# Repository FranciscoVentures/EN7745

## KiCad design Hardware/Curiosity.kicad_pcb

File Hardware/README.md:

Intro
=======

Curiosity™ EN7745
Developed by Francisco Ventures™

Based on the open source hardware project USB Armory MK II | https://github.com/f-secure-foundry/usbarmory/tree/master/hardware/mark-two

DISCLAIMER
=======

Francisco Ventures™ (“Francisco”) is not responsible for typographical or other errors or omissions or for direct, indirect, incidental or consequential damages related to this material or resulting from its use. Francisco makes no warranty or representation respecting this material, which is provided on an "AS IS" basis. FRANCISCO HEREBY DISCLAIMS ALL WARRANTIES OR LIABILITY OF ANY KIND WITH RESPECT THERETO, INCLUDING, WITHOUT LIMITATION, REPRESENTATIONS REGARDING ACCURACY AND COMPLETENESS, ALL IMPLIED WARRANTIES AND CONDITIONS OF MERCHANTABILITY, SUITABILITY OR FITNESS FOR A PARTICULAR PURPOSE, TITLE AND/OR NON-INFRINGEMENT. This material is not designed, intended or authorized for use in medical, life support, life sustaining or nuclear applications or applications in which the failure of the product could result in personal injury, death or property damage. Any party using or selling products for use in any such applications do so at their sole risk and agree that Francisco is not liable, in whole or in part, for any claim or damage arising from such use, and agree to fully indemnify, defend and hold harmless Francisco from and against any and all claims, damages, loss, cost, expense or liability arising out of or in connection with the use or performance of products in such applications.

License
=======

This is an open hardware design licensed under the terms of the CERN Open
Hardware Licence (OHL) v1.2.

You may redistribute and modify this documentation under the terms of the CERN
OHL v.1.2 (http://ohwr.org/cernohl). This documentation is distributed WITHOUT
ANY EXPRESS OR IMPLIED WARRANTY, INCLUDING OF MERCHANTABILITY, SATISFACTORY
QUALITY AND FITNESS FOR A PARTICULAR PURPOSE. Please see the CERN OHL v.1.2 for
applicable conditions.

The following exceptions apply:

- ../lib.snapeda: all files in this directory are imported or modified
from SnapEDA symbols and footprints, therefore the license at
https://www.snapeda.com/about/FAQ/#license applies.

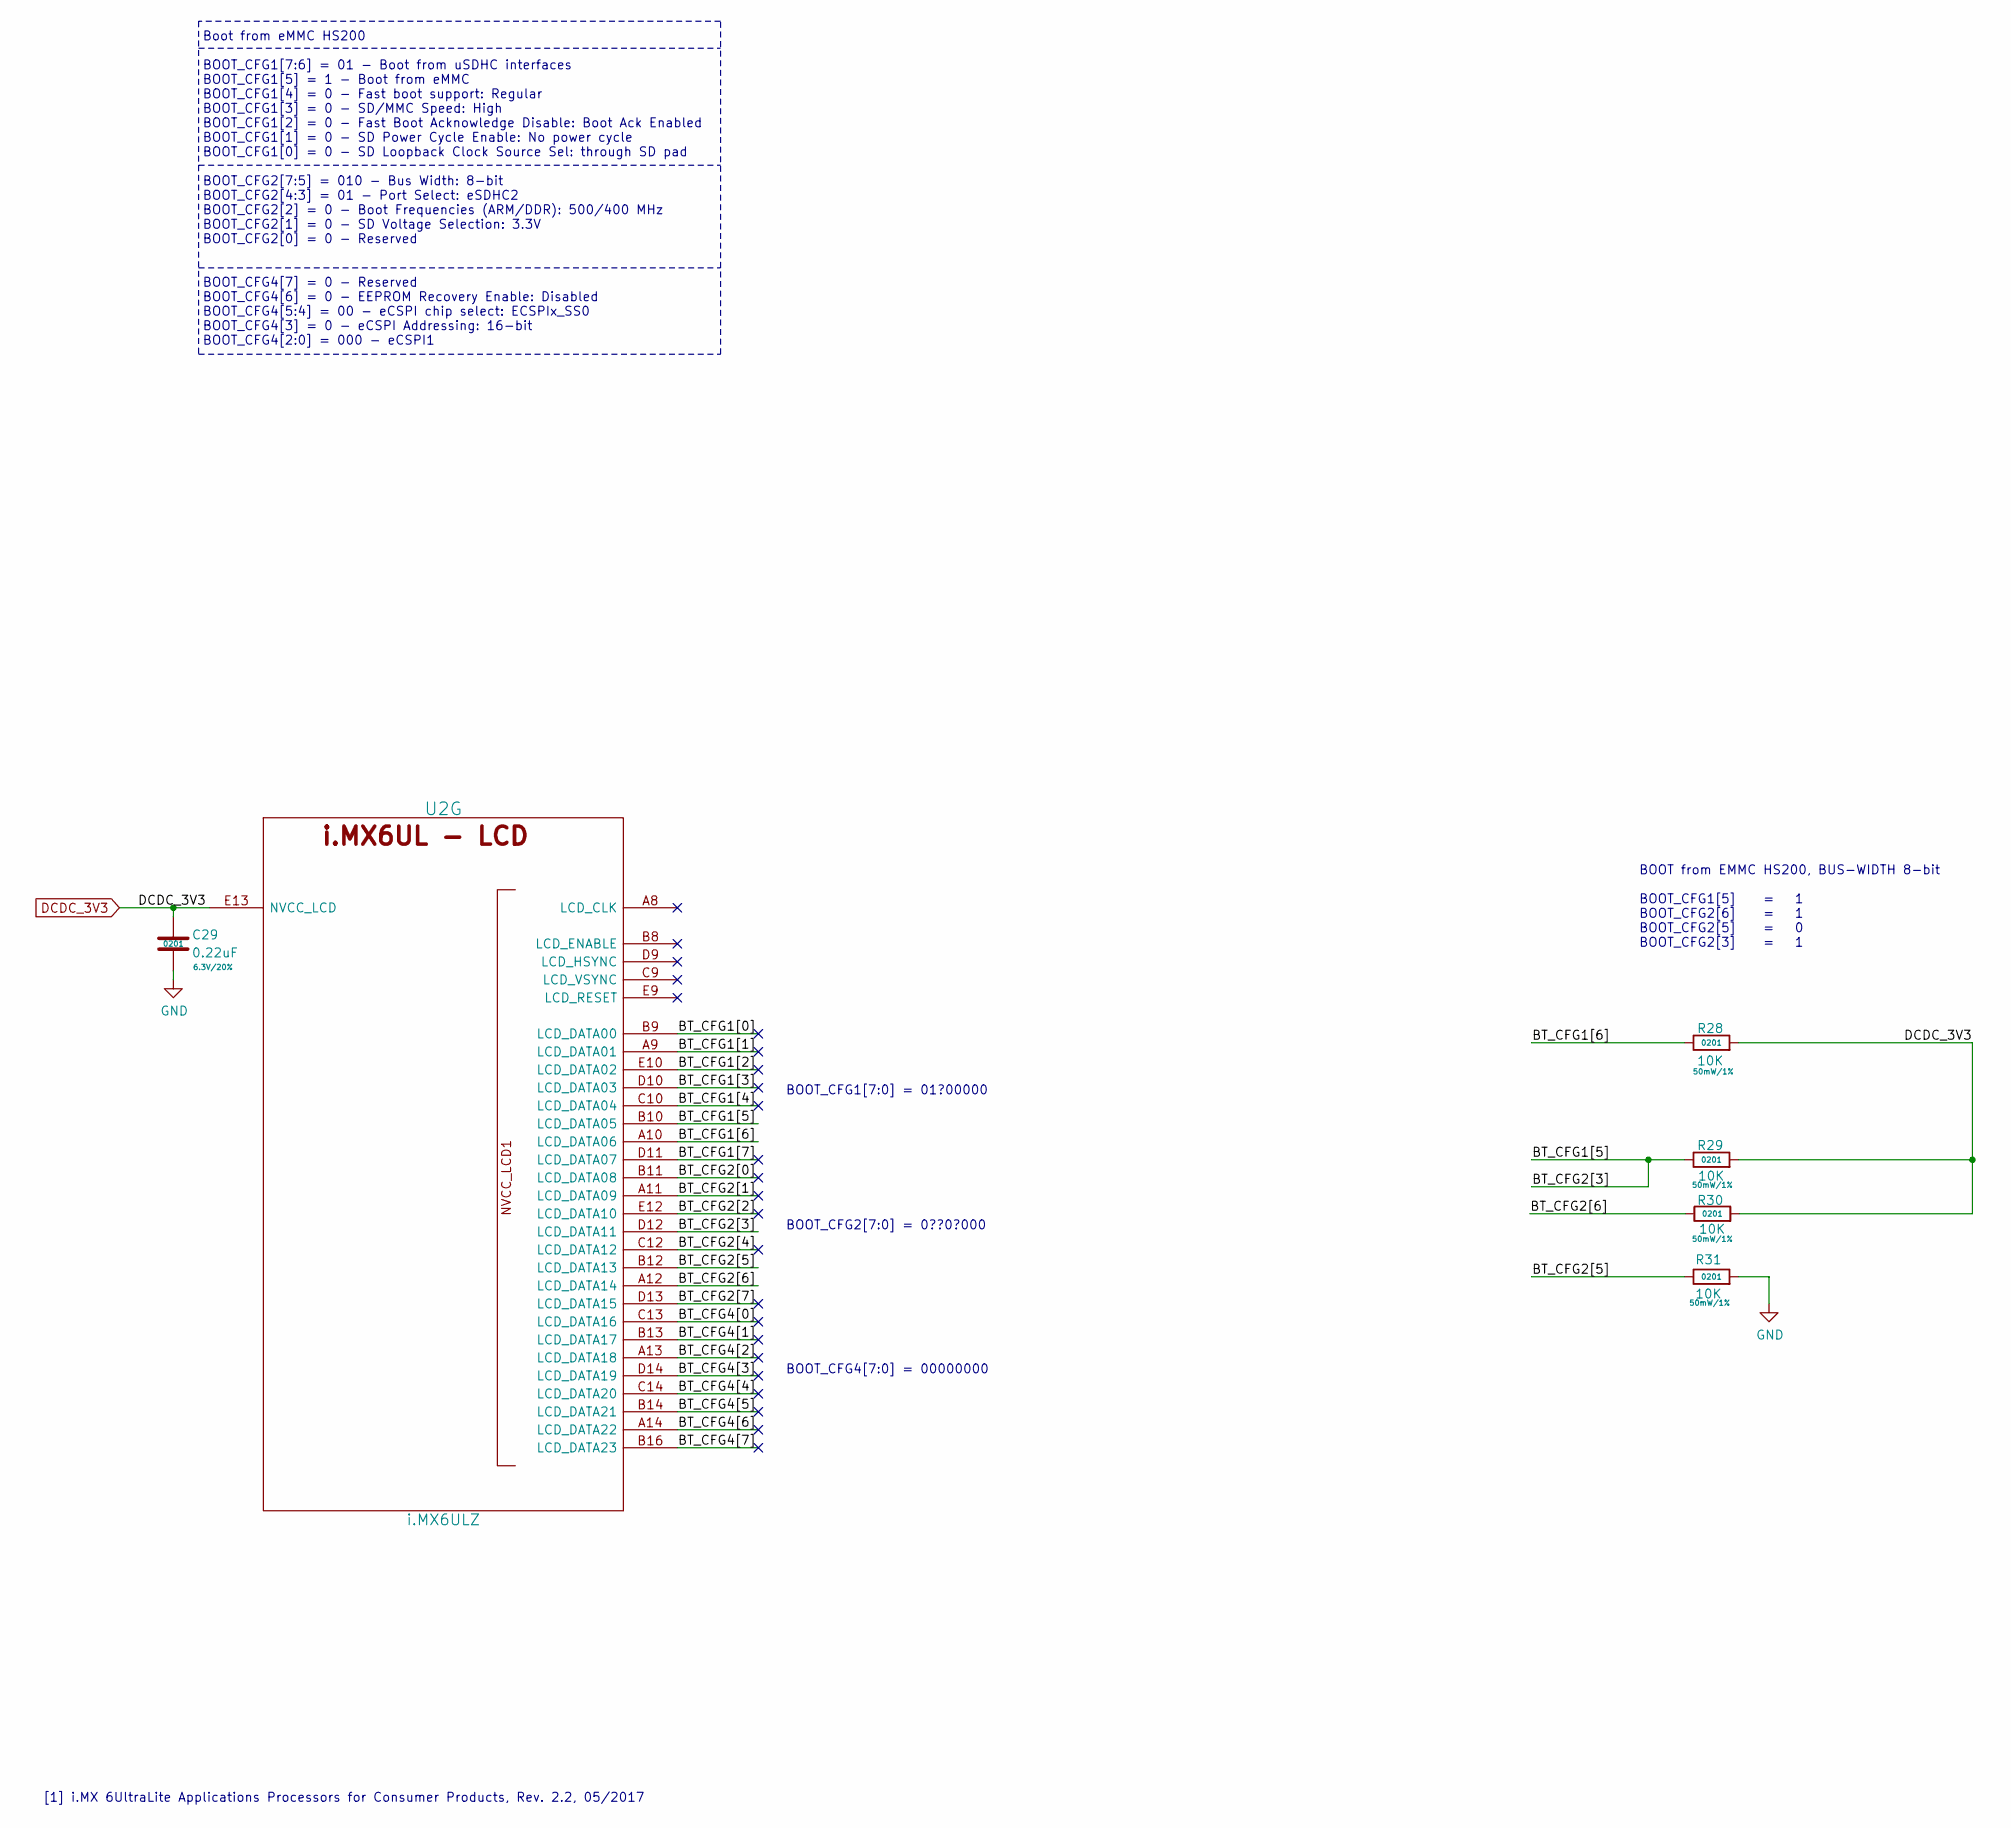
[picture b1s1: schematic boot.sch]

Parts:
C29: 0.22uF; SM0201; Rating 6.3V/20%; Mfg PN GRM033R60J224ME15D; Digi-Key_PN 490-10407-1-ND
R28, R29, R30, R31: 10K; R_0201_0603Metric; Rating 50mW/1%; Mfg PN CRCW020110K0JNED; Digi-Key_PN 541-10KAGCT-ND
U2: i.MX6ULZ; SOT1534-2; Mfg PN MCIMX6Z0DVM09AB; Digi-Key_PN 568-14726-ND

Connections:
/Boot/BT_CFG1[0]: U2.B9 (LCD_DATA00); also elsewhere on the board
/Boot/BT_CFG1[1]: U2.A9 (LCD_DATA01); also elsewhere on the board
/Boot/BT_CFG1[2]: U2.E10 (LCD_DATA02); also elsewhere on the board
/Boot/BT_CFG1[3]: U2.D10 (LCD_DATA03); also elsewhere on the board
/Boot/BT_CFG1[4]: U2.C10 (LCD_DATA04); also elsewhere on the board
/Boot/BT_CFG1[5]: R29.1, U2.B10 (LCD_DATA05), U2.D12 (LCD_DATA11); also elsewhere on the board
/Boot/BT_CFG1[6]: R28.1, U2.A10 (LCD_DATA06); also elsewhere on the board
/Boot/BT_CFG1[7]: U2.D11 (LCD_DATA07); also elsewhere on the board
/Boot/BT_CFG2[0]: U2.B11 (LCD_DATA08); also elsewhere on the board
/Boot/BT_CFG2[1]: U2.A11 (LCD_DATA09); also elsewhere on the board
/Boot/BT_CFG2[2]: U2.E12 (LCD_DATA10); also elsewhere on the board
/Boot/BT_CFG2[4]: U2.C12 (LCD_DATA12); also elsewhere on the board
/Boot/BT_CFG2[5]: R31.1, U2.B12 (LCD_DATA13); also elsewhere on the board
/Boot/BT_CFG2[6]: R30.1, U2.A12 (LCD_DATA14); also elsewhere on the board
/Boot/BT_CFG2[7]: U2.D13 (LCD_DATA15); also elsewhere on the board
/Boot/BT_CFG4[0]: U2.C13 (LCD_DATA16); also elsewhere on the board
/Boot/BT_CFG4[1]: U2.B13 (LCD_DATA17); also elsewhere on the board
/Boot/BT_CFG4[2]: U2.A13 (LCD_DATA18); also elsewhere on the board
/Boot/BT_CFG4[3]: U2.D14 (LCD_DATA19); also elsewhere on the board
/Boot/BT_CFG4[4]: U2.C14 (LCD_DATA20); also elsewhere on the board
/Boot/BT_CFG4[5]: U2.B14 (LCD_DATA21); also elsewhere on the board
/Boot/BT_CFG4[6]: U2.A14 (LCD_DATA22); also elsewhere on the board
/Boot/BT_CFG4[7]: U2.B16 (LCD_DATA23); also elsewhere on the board
DCDC_3V3: C29.1, R28.2, R29.2, R30.2, U2.E13 (NVCC_LCD); also elsewhere on the board
GND: C29.2, R31.2; also elsewhere on the board
unnamed 177: U2.A8 (LCD_CLK); also elsewhere on the board
unnamed 183: U2.B8 (LCD_ENABLE); also elsewhere on the board
unnamed 188: U2.C9 (LCD_VSYNC); also elsewhere on the board
unnamed 193: U2.D9 (LCD_HSYNC); also elsewhere on the board
unnamed 197: U2.E9 (LCD_RESET); also elsewhere on the board

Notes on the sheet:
Boot from eMMC HS200 BOOT_CFG1[7:6] = 01 - Boot from uSDHC interfaces BOOT_CFG1[5] = 1 - Boot from eMMC BOOT_CFG1[4] = 0 - Fast boot support: Regular BOOT_CFG1[3] = 0 - SD/MMC Speed: High BOOT_CFG1[2] = 0 - Fast Boot Acknowledge Disable: Boot Ack Enabled BOOT_CFG1[1] = 0 - SD Power Cycle Enable: No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
BOOT_CFG4[7:0] = 00000000
BOOT from EMMC HS200, BUS-WIDTH 8-bit BOOT_CFG1[5] = 1 BOOT_CFG2[6] = 1 BOOT_CFG2[5] = 0 BOOT_CFG2[3] = 1
BOOT_CFG2[7:0] = 0??0?000
BOOT_CFG1[7:0] = 01?00000
[1] i.MX 6UltraLite Applications Processors for Consumer Products, Rev. 2.2, 05/2017

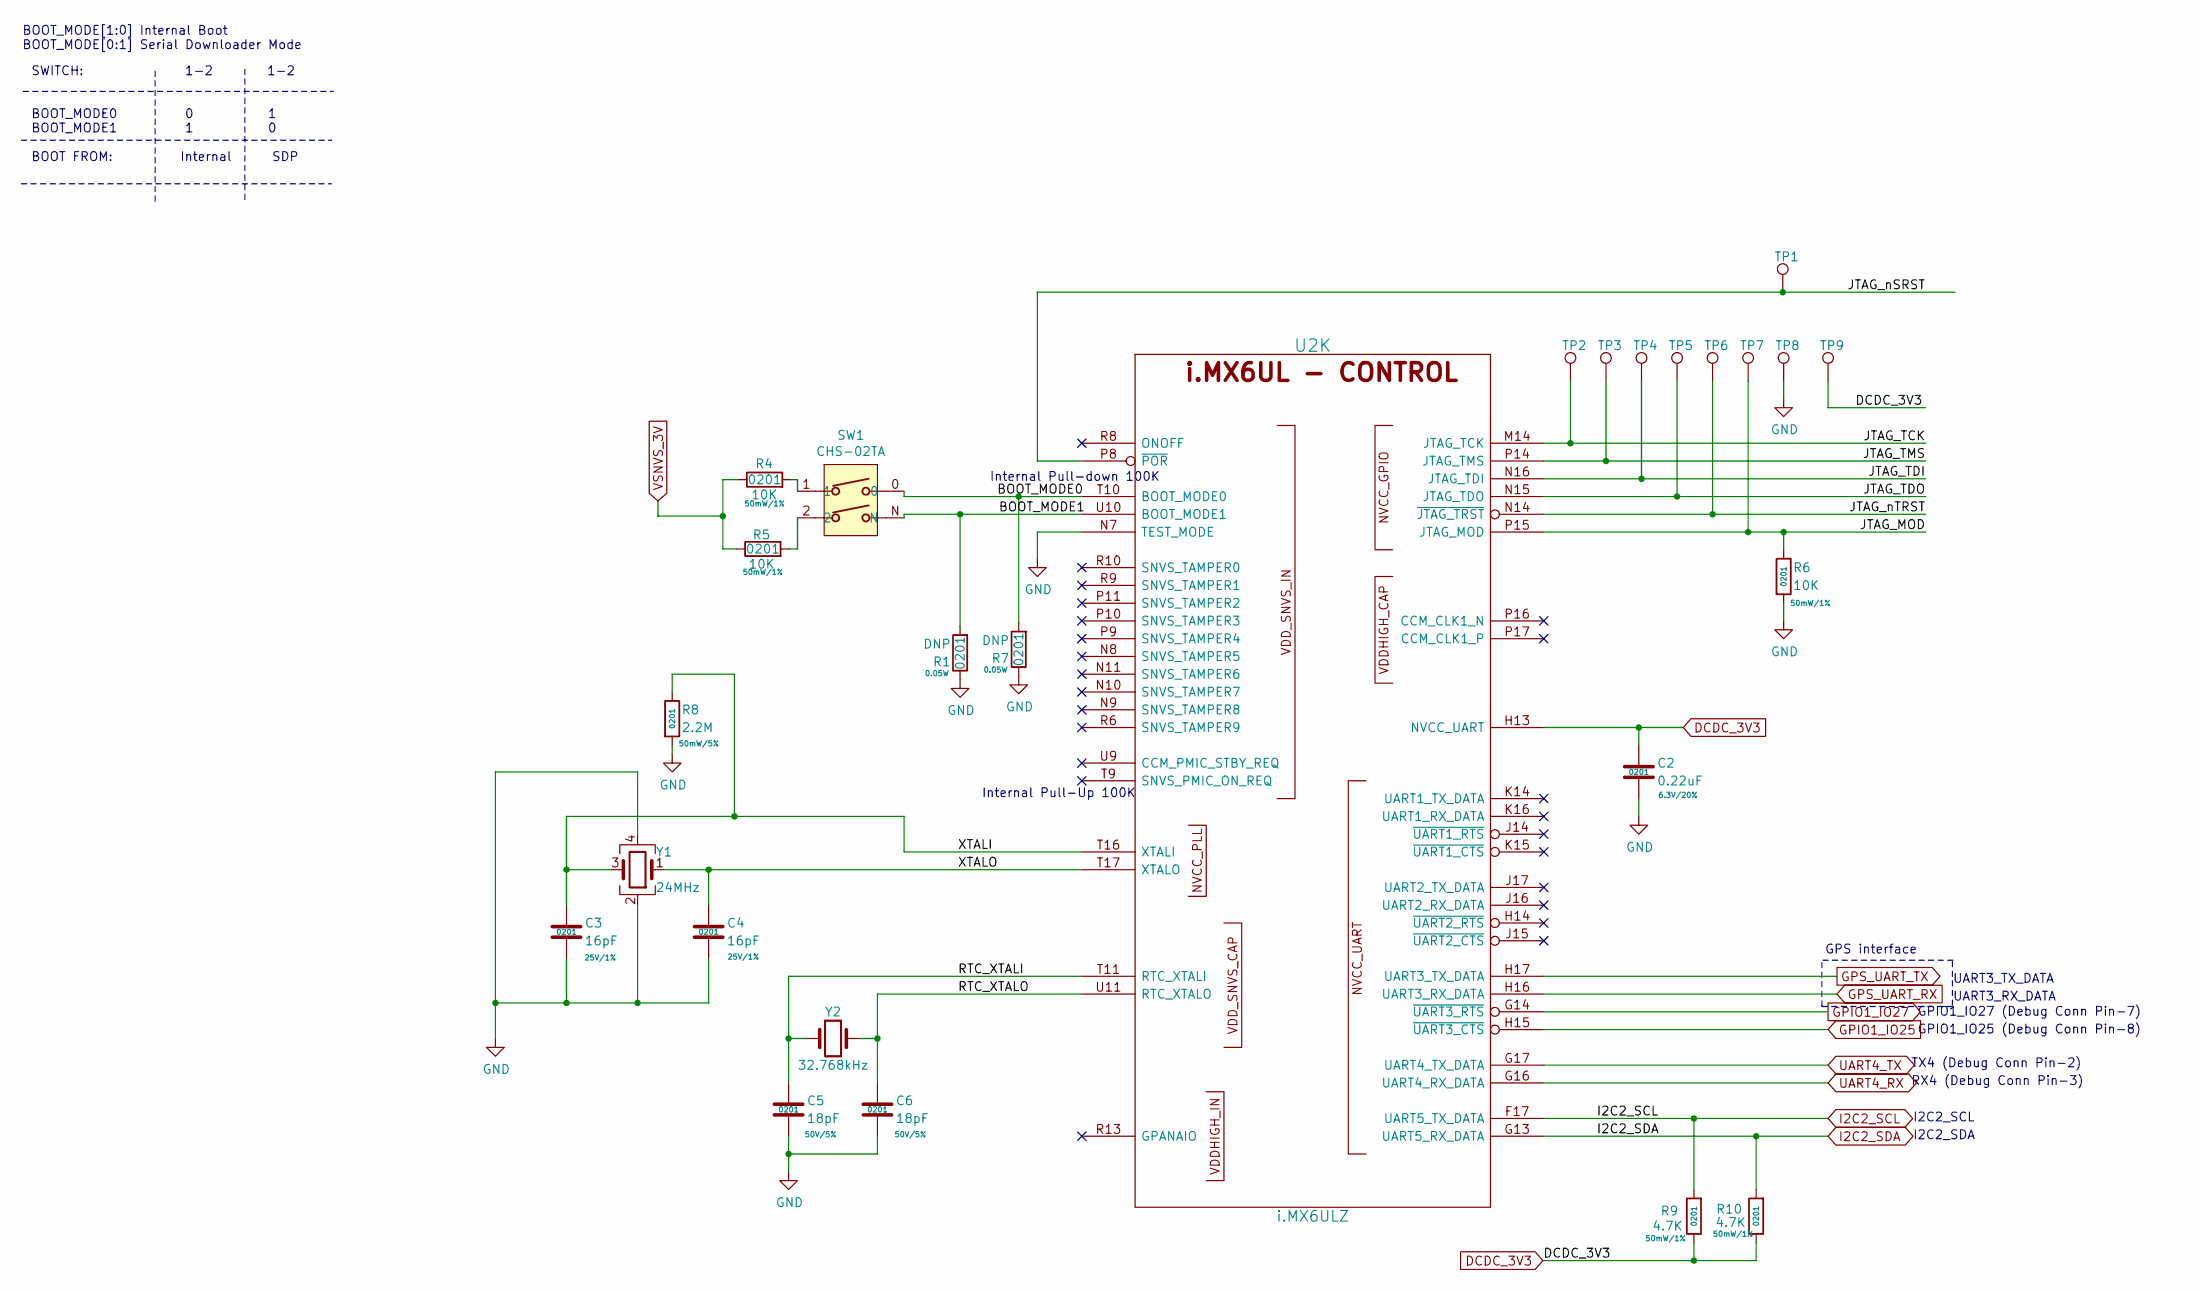
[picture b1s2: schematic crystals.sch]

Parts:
C2: 0.22uF; SM0201; Rating 6.3V/20%; Mfg PN GRM033R60J224ME15D; Digi-Key_PN 490-10407-1-ND
C3, C4: 16pF; SM0201; Rating 25V/1%; Mfg PN CBR02C160F3GAC; Digi-Key_PN 399-8574-1-ND
C5, C6: 18pF; SM0201; Rating 50V/5%; Mfg PN GRM0335C1H180JA01D; Digi-Key_PN 490-6117-1-ND
R1, R7: DNP; R_0201_0603Metric; Rating 0.05W; Mfg PN CRCW02010000Z0ED; Digi-Key_PN 541-0.0AGCT-ND
R4, R5, R6: 10K; R_0201_0603Metric; Rating 50mW/1%; Mfg PN CRCW020110K0JNED; Digi-Key_PN 541-10KAGCT-ND
R8: 2.2M; R_0201_0603Metric; Rating 50mW/5%; Mfg PN RC0201JR-072M2L; Digi-Key_PN YAG2882CT-ND
R9, R10: 4.7K; R_0201_0603Metric; Rating 50mW/1%; Mfg PN CRCW02014K70JNED; Digi-Key_PN 541-4.7KAGCT-ND
SW1: CHS-02TA; Mfg PN CHS-02TA; Digi-Key_PN 563-1005-2-ND
TP1, TP2, TP3, TP4, TP5, TP6, TP7, TP8, TP9: TestPoint; TP
U2: i.MX6ULZ; SOT1534-2; Mfg PN MCIMX6Z0DVM09AB; Digi-Key_PN 568-14726-ND
Y1: 24MHz; TSX-3225; Mfg PN TSX-3225 24.0000MF15X-AC3; Digi-Key_PN SER3635TR-ND
Y2: 32.768kHz; CM7V-T1A; Mfg PN CM7V-T1A-32.768KHZ-12.5PF-20PPM-TB-QA; Digi-Key_PN 2195-CM7V-T1A-32.768KHZ-12.5PF-20PPM-TB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

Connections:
/Crystals/BOOT_MODE0: R7.2, SW1.0, U2.T10 (BOOT_MODE0); also elsewhere on the board
/Crystals/BOOT_MODE1: R1.2, SW1.N, U2.U10 (BOOT_MODE1); also elsewhere on the board
/Crystals/JTAG_MOD: R6.1, TP7.1, U2.P15 (JTAG_MOD); also elsewhere on the board
/Crystals/JTAG_TCK: TP2.1, U2.M14 (JTAG_TCK); also elsewhere on the board
/Crystals/JTAG_TDI: TP4.1, U2.N16 (JTAG_TDI); also elsewhere on the board
/Crystals/JTAG_TDO: TP5.1, U2.N15 (JTAG_TDO); also elsewhere on the board
/Crystals/JTAG_TMS: TP3.1, U2.P14 (JTAG_TMS); also elsewhere on the board
/Crystals/JTAG_nSRST: TP1.1, U2.P8 (~POR); also elsewhere on the board
/Crystals/JTAG_nTRST: TP6.1, U2.N14 (~JTAG_TRST); also elsewhere on the board
/Crystals/RTC_XTALI: C5.1, U2.T11 (RTC_XTALI), Y2.1; also elsewhere on the board
/Crystals/RTC_XTALO: C6.1, U2.U11 (RTC_XTALO), Y2.2; also elsewhere on the board
/Crystals/XTALI: C3.1, R8.1, U2.T16 (XTALI), Y1.3; also elsewhere on the board
/Crystals/XTALO: C4.1, U2.T17 (XTALO), Y1.1; also elsewhere on the board
DCDC_3V3: C2.1, R9.1, R10.1, TP9.1, U2.H13 (NVCC_UART); also elsewhere on the board
GND: C2.2, C3.2, C4.2, C5.2, C6.2, R1.1, R6.2, R7.1, R8.2, TP8.1, U2.N7 (TEST_MODE), Y1.2, Y1.4; also elsewhere on the board
GPIO1_IO25: U2.H15 (~UART3_CTS); also elsewhere on the board
GPIO1_IO27: U2.G14 (~UART3_RTS); also elsewhere on the board
GPS_UART_RX: U2.H16 (UART3_RX_DATA); also elsewhere on the board
GPS_UART_TX: U2.H17 (UART3_TX_DATA); also elsewhere on the board
I2C2_SCL: R9.2, U2.F17 (UART5_TX_DATA); also elsewhere on the board
I2C2_SDA: R10.2, U2.G13 (UART5_RX_DATA); also elsewhere on the board
unnamed: R4.2, SW1.1
unnamed: R5.2, SW1.2
unnamed 209: U2.H14 (~UART2_RTS); also elsewhere on the board
unnamed 211: U2.J14 (~UART1_RTS); also elsewhere on the board
unnamed 212: U2.J15 (~UART2_CTS); also elsewhere on the board
unnamed 213: U2.J16 (UART2_RX_DATA); also elsewhere on the board
unnamed 214: U2.J17 (UART2_TX_DATA); also elsewhere on the board
unnamed 215: U2.K14 (UART1_TX_DATA); also elsewhere on the board
unnamed 216: U2.K15 (~UART1_CTS); also elsewhere on the board
unnamed 217: U2.K16 (UART1_RX_DATA); also elsewhere on the board
unnamed 218: U2.N8 (SNVS_TAMPER5); also elsewhere on the board
unnamed 219: U2.N9 (SNVS_TAMPER8); also elsewhere on the board
unnamed 220: U2.N10 (SNVS_TAMPER7); also elsewhere on the board
unnamed 221: U2.N11 (SNVS_TAMPER6); also elsewhere on the board
unnamed 222: U2.P9 (SNVS_TAMPER4); also elsewhere on the board
unnamed 223: U2.P10 (SNVS_TAMPER3); also elsewhere on the board
unnamed 224: U2.P11 (SNVS_TAMPER2); also elsewhere on the board
unnamed 225: U2.P16 (CCM_CLK1_N); also elsewhere on the board
unnamed 226: U2.P17 (CCM_CLK1_P); also elsewhere on the board
unnamed 227: U2.R6 (SNVS_TAMPER9); also elsewhere on the board
unnamed 228: U2.R8 (ONOFF); also elsewhere on the board
unnamed 229: U2.R9 (SNVS_TAMPER1); also elsewhere on the board
unnamed 230: U2.R10 (SNVS_TAMPER0); also elsewhere on the board
unnamed 231: U2.R13 (GPANAIO); also elsewhere on the board
unnamed 232: U2.T9 (SNVS_PMIC_ON_REQ); also elsewhere on the board
unnamed 234: U2.U9 (CCM_PMIC_STBY_REQ); also elsewhere on the board
UART4_RX: U2.G16 (UART4_RX_DATA); also elsewhere on the board
UART4_TX: U2.G17 (UART4_TX_DATA); also elsewhere on the board
VSNVS_3V: R4.1, R5.1; also elsewhere on the board

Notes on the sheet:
BOOT_MODE[1:0] Internal Boot BOOT_MODE[0:1] Serial Downloader Mode
GPS interface
UART3_TX_DATA
UART3_RX_DATA
SWITCH: 1-2 1-2 BOOT_MODE0 0 1 BOOT_MODE1 1 0 BOOT FROM: Internal SDP
GPIO1_IO27 (Debug Conn Pin-7)
RX4 (Debug Conn Pin-3)
TX4 (Debug Conn Pin-2)
I2C2_SDA
I2C2_SCL
Internal Pull-down 100K
Internal Pull-Up 100K
GPIO1_IO25 (Debug Conn Pin-8)

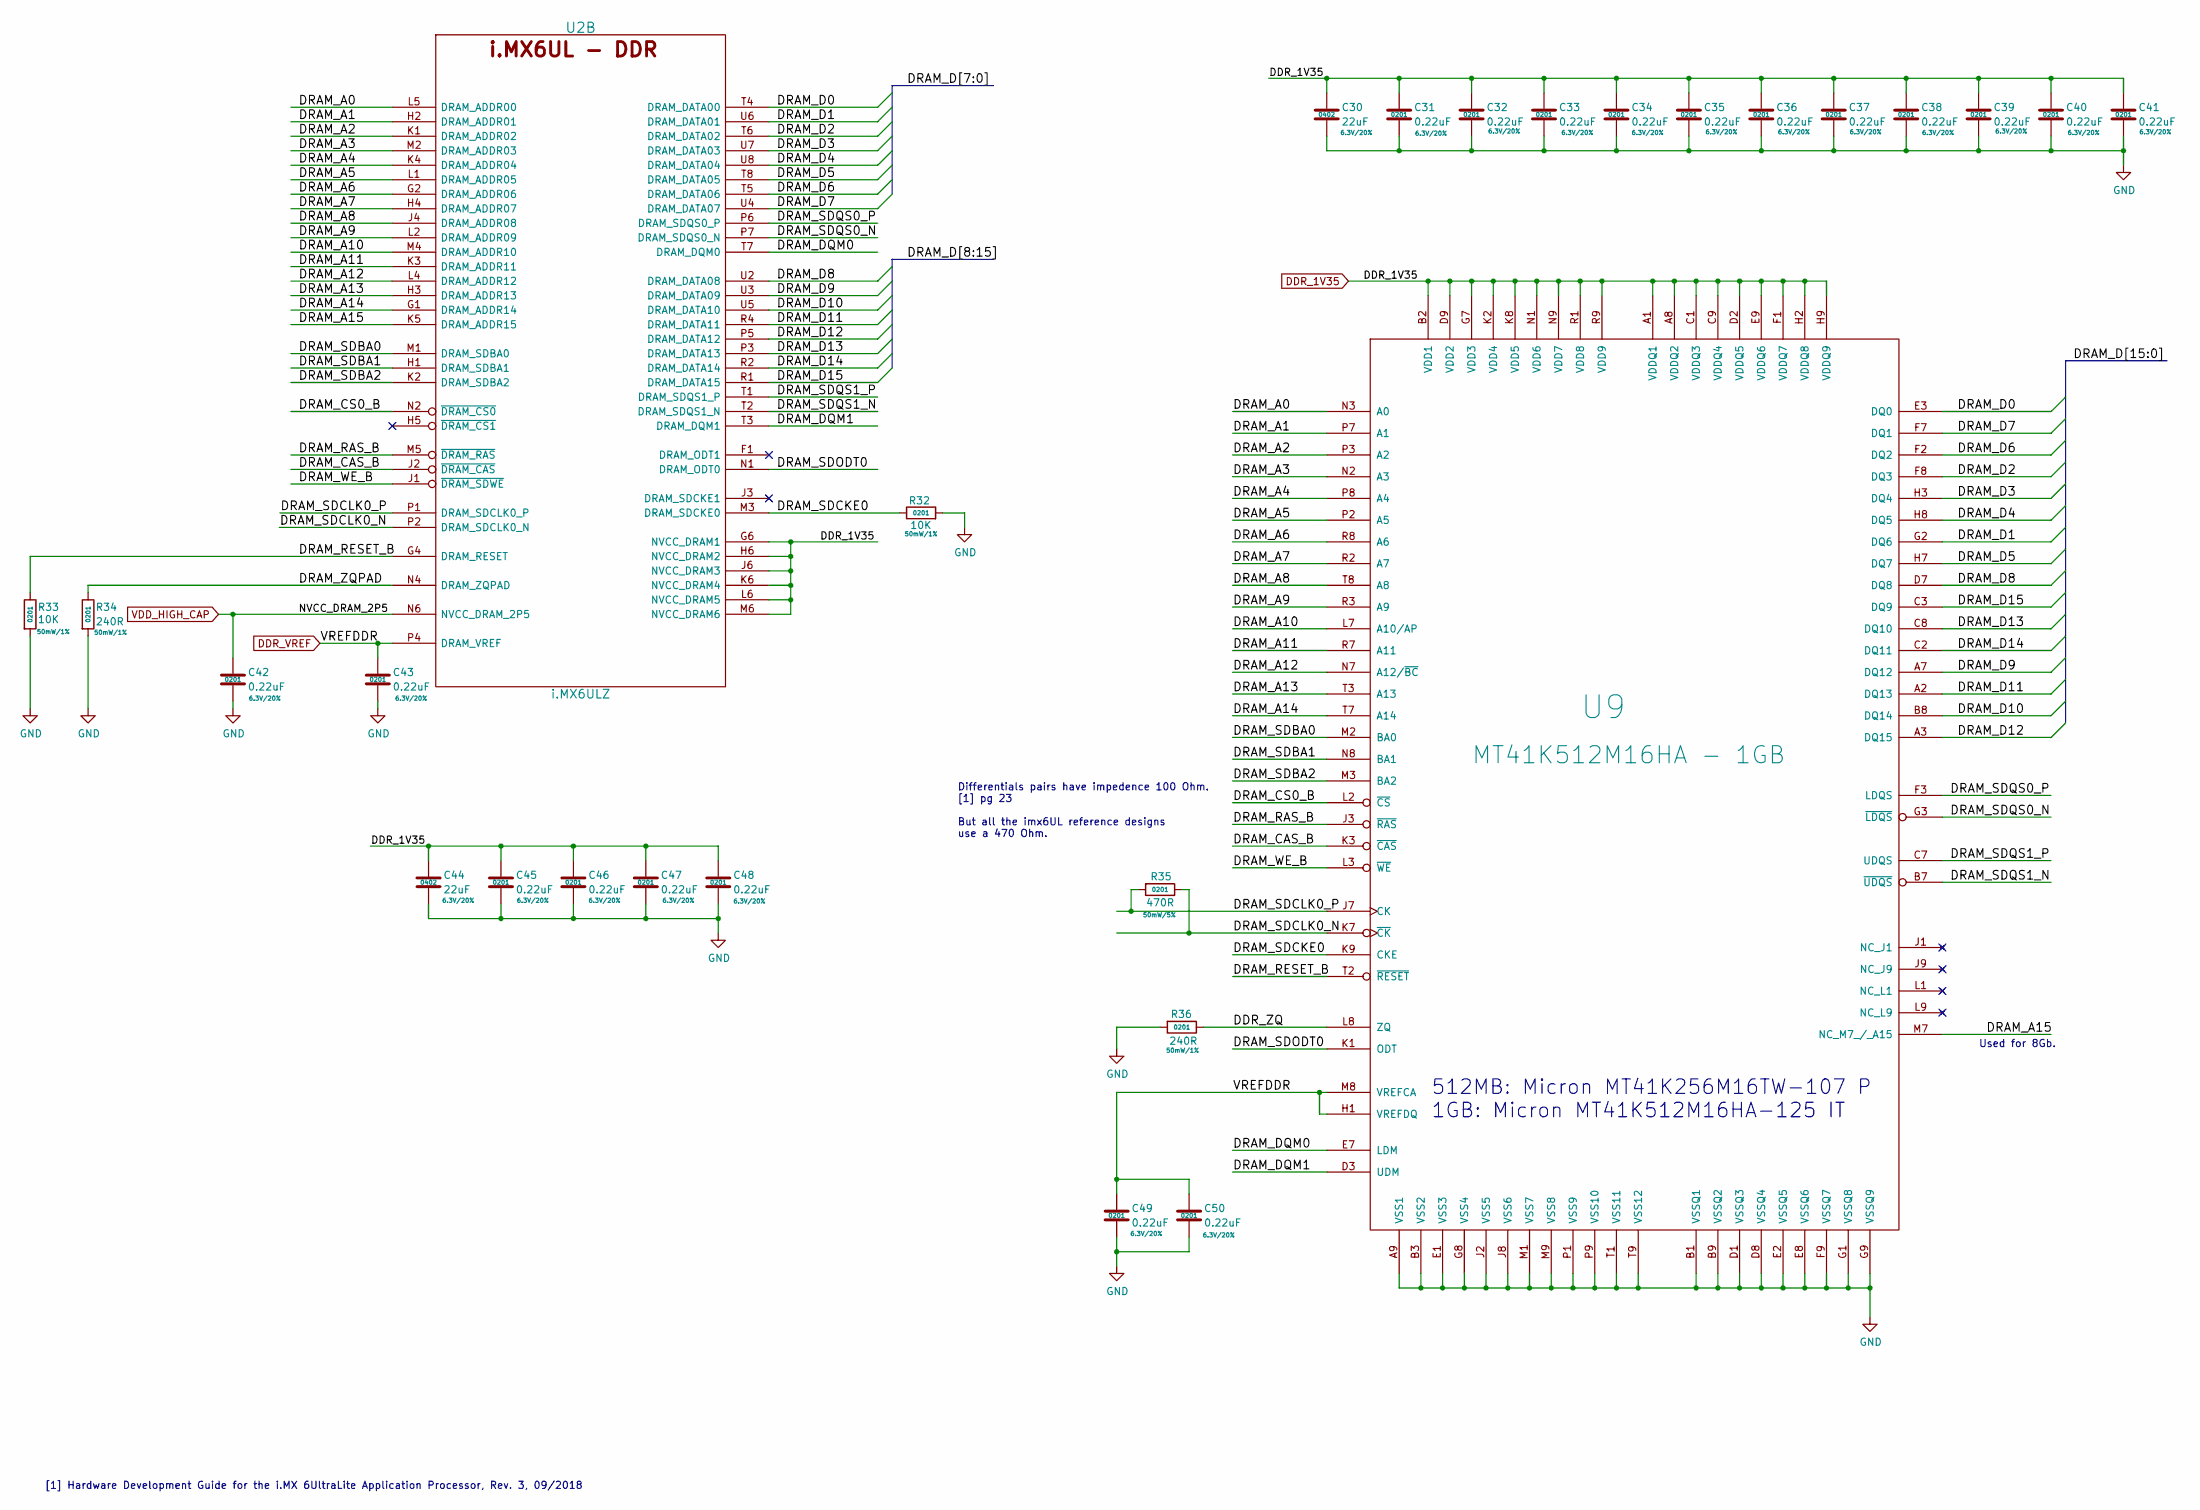
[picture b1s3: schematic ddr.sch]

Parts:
C30, C44: 22uF; SM0402; Rating 6.3V/20%; Mfg PN CL05A226MQ5N6J8; Digi-Key_PN 1276-7090-1-ND
C31, C32, C33, C34, C35, C36, C37, C38, C39, C40, C41, C42, C43, C45, C46, C47, C48, C49, C50: 0.22uF; SM0201; Rating 6.3V/20%; Mfg PN GRM033R60J224ME15D; Digi-Key_PN 490-10407-1-ND
R32, R33: 10K; R_0201_0603Metric; Rating 50mW/1%; Mfg PN CRCW020110K0JNED; Digi-Key_PN 541-10KAGCT-ND
R34, R36: 240R; R_0201_0603Metric; Rating 50mW/1%; Mfg PN CRCW0201240RFNED; Digi-Key_PN 541-2949-1-ND
R35: 470R; R_0201_0603Metric; Rating 50mW/5%; Mfg PN CRCW0201470RJNED; Digi-Key_PN 541-470AGCT-ND
U2: i.MX6ULZ; SOT1534-2; Mfg PN MCIMX6Z0DVM09AB; Digi-Key_PN 568-14726-ND
U9: MT41K512M16HA - 1GB; MICRON-FBGA-96; Mfg PN MT41K512M16HA-125 IT:A; Digi-Key_PN MT41K512M16HA-125IT:A-ND

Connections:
/DDR/DDR_ZQ: R36.1, U9.L8 (ZQ)
/DDR/DRAM_A0: U2.L5 (DRAM_ADDR00), U9.N3 (A0); also elsewhere on the board
/DDR/DRAM_A1: U2.H2 (DRAM_ADDR01), U9.P7 (A1); also elsewhere on the board
/DDR/DRAM_A2: U2.K1 (DRAM_ADDR02), U9.P3 (A2); also elsewhere on the board
/DDR/DRAM_A3: U2.M2 (DRAM_ADDR03), U9.N2 (A3); also elsewhere on the board
/DDR/DRAM_A4: U2.K4 (DRAM_ADDR04), U9.P8 (A4); also elsewhere on the board
/DDR/DRAM_A5: U2.L1 (DRAM_ADDR05), U9.P2 (A5); also elsewhere on the board
/DDR/DRAM_A6: U2.G2 (DRAM_ADDR06), U9.R8 (A6); also elsewhere on the board
/DDR/DRAM_A7: U2.H4 (DRAM_ADDR07), U9.R2 (A7); also elsewhere on the board
/DDR/DRAM_A8: U2.J4 (DRAM_ADDR08), U9.T8 (A8); also elsewhere on the board
/DDR/DRAM_A9: U2.L2 (DRAM_ADDR09), U9.R3 (A9); also elsewhere on the board
/DDR/DRAM_A10: U2.M4 (DRAM_ADDR10), U9.L7 (A10/AP); also elsewhere on the board
/DDR/DRAM_A11: U2.K3 (DRAM_ADDR11), U9.R7 (A11); also elsewhere on the board
/DDR/DRAM_A12: U2.L4 (DRAM_ADDR12), U9.N7 (A12/~BC); also elsewhere on the board
/DDR/DRAM_A13: U2.H3 (DRAM_ADDR13), U9.T3 (A13); also elsewhere on the board
/DDR/DRAM_A14: U2.G1 (DRAM_ADDR14), U9.T7 (A14); also elsewhere on the board
/DDR/DRAM_A15: U2.K5 (DRAM_ADDR15), U9.M7 (NC_M7_/_A15); also elsewhere on the board
/DDR/DRAM_CAS_B: U2.J2 (~DRAM_CAS), U9.K3 (~CAS); also elsewhere on the board
/DDR/DRAM_CS0_B: U2.N2 (~DRAM_CS0), U9.L2 (~CS); also elsewhere on the board
/DDR/DRAM_D0: U2.T4 (DRAM_DATA00), U9.E3 (DQ0); also elsewhere on the board
/DDR/DRAM_D1: U2.U6 (DRAM_DATA01), U9.G2 (DQ6); also elsewhere on the board
/DDR/DRAM_D2: U2.T6 (DRAM_DATA02), U9.F8 (DQ3); also elsewhere on the board
/DDR/DRAM_D3: U2.U7 (DRAM_DATA03), U9.H3 (DQ4); also elsewhere on the board
/DDR/DRAM_D4: U2.U8 (DRAM_DATA04), U9.H8 (DQ5); also elsewhere on the board
/DDR/DRAM_D5: U2.T8 (DRAM_DATA05), U9.H7 (DQ7); also elsewhere on the board
/DDR/DRAM_D6: U2.T5 (DRAM_DATA06), U9.F2 (DQ2); also elsewhere on the board
/DDR/DRAM_D7: U2.U4 (DRAM_DATA07), U9.F7 (DQ1); also elsewhere on the board
/DDR/DRAM_D8: U2.U2 (DRAM_DATA08), U9.D7 (DQ8); also elsewhere on the board
/DDR/DRAM_D9: U2.U3 (DRAM_DATA09), U9.A7 (DQ12); also elsewhere on the board
/DDR/DRAM_D10: U2.U5 (DRAM_DATA10), U9.B8 (DQ14); also elsewhere on the board
/DDR/DRAM_D11: U2.R4 (DRAM_DATA11), U9.A2 (DQ13); also elsewhere on the board
/DDR/DRAM_D12: U2.P5 (DRAM_DATA12), U9.A3 (DQ15); also elsewhere on the board
/DDR/DRAM_D13: U2.P3 (DRAM_DATA13), U9.C8 (DQ10); also elsewhere on the board
/DDR/DRAM_D14: U2.R2 (DRAM_DATA14), U9.C2 (DQ11); also elsewhere on the board
/DDR/DRAM_D15: U2.R1 (DRAM_DATA15), U9.C3 (DQ9); also elsewhere on the board
/DDR/DRAM_DQM0: U2.T7 (DRAM_DQM0), U9.E7 (LDM); also elsewhere on the board
/DDR/DRAM_DQM1: U2.T3 (DRAM_DQM1), U9.D3 (UDM); also elsewhere on the board
/DDR/DRAM_RAS_B: U2.M5 (~DRAM_RAS), U9.J3 (~RAS); also elsewhere on the board
/DDR/DRAM_RESET_B: R33.1, U2.G4 (DRAM_RESET), U9.T2 (~RESET); also elsewhere on the board
/DDR/DRAM_SDBA0: U2.M1 (DRAM_SDBA0), U9.M2 (BA0); also elsewhere on the board
/DDR/DRAM_SDBA1: U2.H1 (DRAM_SDBA1), U9.N8 (BA1); also elsewhere on the board
/DDR/DRAM_SDBA2: U2.K2 (DRAM_SDBA2), U9.M3 (BA2); also elsewhere on the board
/DDR/DRAM_SDCKE0: R32.1, U2.M3 (DRAM_SDCKE0), U9.K9 (CKE); also elsewhere on the board
/DDR/DRAM_SDCLK0_N: R35.1, U2.P2 (DRAM_SDCLK0_N), U9.K7 (~CK); also elsewhere on the board
/DDR/DRAM_SDCLK0_P: R35.2, U2.P1 (DRAM_SDCLK0_P), U9.J7 (CK); also elsewhere on the board
/DDR/DRAM_SDODT0: U2.N1 (DRAM_ODT0), U9.K1 (ODT); also elsewhere on the board
/DDR/DRAM_SDQS0_N: U2.P7 (DRAM_SDQS0_N), U9.G3 (~LDQS); also elsewhere on the board
/DDR/DRAM_SDQS0_P: U2.P6 (DRAM_SDQS0_P), U9.F3 (LDQS); also elsewhere on the board
/DDR/DRAM_SDQS1_N: U2.T2 (DRAM_SDQS1_N), U9.B7 (~UDQS); also elsewhere on the board
/DDR/DRAM_SDQS1_P: U2.T1 (DRAM_SDQS1_P), U9.C7 (UDQS); also elsewhere on the board
/DDR/DRAM_WE_B: U2.J1 (~DRAM_SDWE), U9.L3 (~WE); also elsewhere on the board
/DDR/DRAM_ZQPAD: R34.1, U2.N4 (DRAM_ZQPAD); also elsewhere on the board
DDR_1V35: C30.1, C31.1, C32.1, C33.1, C34.1, C35.1, C36.1, C37.1, C38.1, C39.1, C40.1, C41.1, C44.1, C45.1, C46.1, C47.1, C48.1, U2.G6 (NVCC_DRAM1), U2.H6 (NVCC_DRAM2), U2.J6 (NVCC_DRAM3), U2.K6 (NVCC_DRAM4), U2.L6 (NVCC_DRAM5), U2.M6 (NVCC_DRAM6), U9.A1 (VDDQ1), U9.A8 (VDDQ2), U9.B2 (VDD1), U9.C1 (VDDQ3), U9.C9 (VDDQ4), U9.D2 (VDDQ5), U9.D9 (VDD2), U9.E9 (VDDQ6), U9.F1 (VDDQ7), U9.G7 (VDD3), U9.H2 (VDDQ8), U9.H9 (VDDQ9), U9.K2 (VDD4), U9.K8 (VDD5), U9.N1 (VDD6), U9.N9 (VDD7), U9.R1 (VDD8), U9.R9 (VDD9); also elsewhere on the board
DDR_VREF: C43.1, C49.1, C50.1, U2.P4 (DRAM_VREF), U9.H1 (VREFDQ), U9.M8 (VREFCA); also elsewhere on the board
GND: C30.2, C31.2, C32.2, C33.2, C34.2, C35.2, C36.2, C37.2, C38.2, C39.2, C40.2, C41.2, C42.2, C43.2, C44.2, C45.2, C46.2, C47.2, C48.2, C49.2, C50.2, R32.2, R33.2, R34.2, R36.2, U9.A9 (VSS1), U9.B1 (VSSQ1), U9.B3 (VSS2), U9.B9 (VSSQ2), U9.D1 (VSSQ3), U9.D8 (VSSQ4), U9.E1 (VSS3), U9.E2 (VSSQ5), U9.E8 (VSSQ6), U9.F9 (VSSQ7), U9.G1 (VSSQ8), U9.G8 (VSS4), U9.G9 (VSSQ9), U9.J2 (VSS5), U9.J8 (VSS6), U9.M1 (VSS7), U9.M9 (VSS8), U9.P1 (VSS9), U9.P9 (VSS10), U9.T1 (VSS11), U9.T9 (VSS12); also elsewhere on the board
unnamed 202: U2.F1 (DRAM_ODT1); also elsewhere on the board
unnamed 208: U2.H5 (~DRAM_CS1); also elsewhere on the board
unnamed 210: U2.J3 (DRAM_SDCKE1); also elsewhere on the board
VDD_HIGH_CAP: C42.1, U2.N6 (NVCC_DRAM_2P5); also elsewhere on the board

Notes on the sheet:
Used for 8Gb.
512MB: Micron MT41K256M16TW-107 P 1GB: Micron MT41K512M16HA-125 IT
[1] Hardware Development Guide for the i.MX 6UltraLite Application Processor, Rev. 3, 09/2018
Differentials pairs have impedence 100 Ohm. [1] pg 23 But all the imx6UL reference designs use a 470 Ohm.

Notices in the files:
Hardware/Curiosity.kicad_pcb:
Copyright © Francisco Ventures
License: CERN OHL v1.2
Hardware/boot.sch:
Copyright © 2019 F-Secure
parts and their libraries:
Copyright 2016 Accelerated Designs. All rights reserved.
